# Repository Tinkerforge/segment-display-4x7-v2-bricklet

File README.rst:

Segment Display 4x7 Bricklet 2.0
================================

This repository contains the firmware source code and the hardware design
files. The documentation generator configs can be found at
https://github.com/Tinkerforge/generators

Repository Content
------------------

software/:
 * examples/: Examples for all supported languages
 * build/: Compiled files
 * src/: Source code of firmware
 * Makefile: Makefile to build project

hardware/:
 * Contains KiCad project files and additionally schematics as PDF

datasheets/:
 * Contains datasheets for sensors and complex ICs that are used

Hardware
--------

The hardware is designed with the open source EDA Suite KiCad
(http://www.kicad.org). Before you are able to open the files,
you have to install the Tinkerforge kicad-libraries
(https://github.com/Tinkerforge/kicad-libraries). You can either clone
them directly in hardware/ or clone them in a separate folder and
symlink them into hardware/
(ln -s kicad_path/kicad-libraries project_path/hardware). After that you
can open the .pro file in hardware/ with KiCad and from there view and
modify the schematics and the PCB layout.

Software
--------

If you want to do your own Brick/Bricklet firmware development we highly
recommend that you use our build environment setup script and read the
tutorial (https://www.tinkerforge.com/en/doc/Tutorials/Tutorial_Build_Environment/Tutorial.html).

To compile the C code we recommend you to install the newest GNU Arm Embedded
Toolchain (https://launchpad.net/gcc-arm-embedded/+download).
You also need to install bricklib2 (https://github.com/Tinkerforge/bricklib2).

You can either clone it directly in software/src/ or clone it in a
separate folder and symlink it into software/src/
(ln -s bricklib_path/bricklib2 project_path/software/src/). Finally make sure to
have CMake installed (http://www.cmake.org/cmake/resources/software.html).

After that you can build the firmware by invoking make in software/.
The firmware (.zbin) can then be found in software/build/ and uploaded
with brickv (click button "Flashing" on start screen).

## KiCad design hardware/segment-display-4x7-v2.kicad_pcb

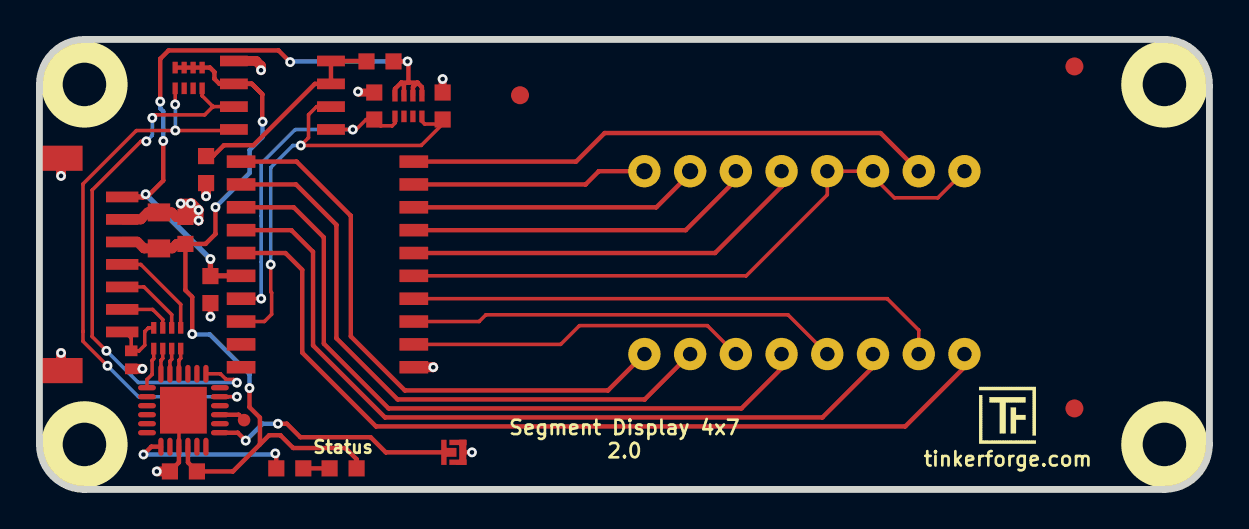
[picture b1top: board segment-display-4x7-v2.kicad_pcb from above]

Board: 2 copper layers, 65.0 x 25.0 mm, 30 parts (0 on the bottom side), 34 nets.

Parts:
C1, C3: 1nF; C0603F
C2: 220pF; C0402F
C4: 10uF; C0805
C5, C7, C8: 100nF; C0603F
C6: 1uF; C0603F
D1: blue; D0603F
Fiducial_Mark: VAL**; Fiducial_Mark
Fiducial_Mark#2, Fiducial_Mark#3: VAL**; Fiducial_Mark
P1: CON-SENSOR2
P2: DEBUG; DEBUG_PAD
P3: BOOT; SolderJumper
R1: 1k; R0603F
R2: 200k; R0603F
RP1: 82; 4X0402
RP2, RP3: 2k2; 4X0402
U1: XMC1100; QFN24-4x4mm-0.5mm
U2: TM1637; SOP20
U3: SEGMENT_4X7
U4, U5, U6, U7: DRILL; DRILL_NP
U8: PCA9306D; SOIC8
VAL: WEEE_7mm
VAL#2: CE_5mm

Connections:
+5V: C5.1, P1.1, R2.2, RP2.1, RP2.2, RP2.3, RP2.4, U2.16
COM1: U2.11, U3.1
COM2: U2.12, U3.2
COM3: U2.14, U3.6
COM4: U2.15, U3.8
COMD1D2: U2.13, U3.4
COMD3: U2.10, U3.10
GND: C1.1, C2.2, C3.1, C4.2, C5.2, C6.2, C7.2, C8.2, P1.2, P1.EP, P3.1, U1.9, U1.EXP, U2.1, U8.1
unnamed: C2.1, P1.7, RP1.4
unnamed: C8.1, R2.1, U8.7, U8.8
unnamed: D1.2, R1.2
unnamed: P1.4, RP1.1
unnamed: P1.5, RP1.2
unnamed: P1.6, RP1.3
unnamed: P2.1, U1.15
unnamed: P3.2, U1.13
unnamed: R1.1, U1.7
unnamed: U2.2, U3.3
unnamed: U2.3, U3.5
unnamed: U2.4, U3.7
unnamed: U2.5, U3.9, U3.11, U3.12
unnamed: U2.6, U3.13
unnamed: U2.7, U3.14
unnamed: U2.8, U3.15
unnamed: U2.9, U3.16
S-CLK: RP1.7, U1.23
S-CS: RP1.8, U1.22
S-MISO: RP1.5, U1.1
S-MOSI: RP1.6, U1.24
SCL: RP3.8, U1.19, U8.3
SCL2: C3.2, RP2.8, U2.18, U8.6
SDA: RP3.5, U1.17, U8.4
SDA2: C1.2, RP2.5, U2.17, U8.5
VCC: C4.1, C6.1, C7.1, D1.1, P1.3, RP3.1, RP3.2, RP3.3, RP3.4, U1.10, U8.2

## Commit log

2018-06-25 Add datasheets
2018-06-25 Use English language datasheet instead of Chinese
2018-06-25 Add schematic
2018-06-25 Rename files
2018-06-25 Add layout (tbc)
2018-06-27 Add layout
2018-06-28 Fix readme
2018-06-28 Add .gitignore
2018-07-04 Change value and size of pullup
2018-07-11 Add pullup resistors and change existing footprint to 4X0402
2018-07-11 Fix origin
2018-07-25 Add auto-generated stub firmware
2019-01-11 Add PCA9306 datasheet
2019-01-17 fix library links in schematic
2019-01-17 segment driver reconnect, control all available leds
2019-01-22 remove open gnd circuit
2019-02-21 Add API implementation and TM1637 driver
2019-02-21 Replace KHN40392ASR1D-2 with LTC-4627JR
2019-02-22 changed processor to XMC1100
2019-02-25 Fix segments for colon dots and tick mark
2019-02-25 Remove unnecessary comments
2019-03-28 mqtt: Fix whitespace.
2019-03-29 Add examples.
2019-04-23 Use bool for segment
2019-04-23 Add TM1637 config
2019-04-23 Turn off colon and tick when setting counter
2019-04-23 Fix function name
2019-04-23 Fix value/segment type mixup
2019-04-30 Turn logging off
2019-05-09 add schematic and sym lib
2019-05-10 add cutout drawing
2019-05-13 add 3d files, rename
2019-05-13 fix file names
2019-05-20 Update auto-generated rust example
2019-05-20 Release Bricklet
2019-05-20 Use correct hash for v2.0.0
2019-05-20 rust: Use merged imports again.
2019-05-20 shell: Escape positional argument to avoid option parsing
2019-05-29 Increase version for new release (changes in bricklib2)
2019-05-29 Add rev to changelog
2020-01-13 examples: Use python3 input instead of python2 raw_input.
2020-01-13 examples: mqtt: Remove trailing whitespace.
2020-03-16 Whitespace
2020-03-23 mqtt: Update for loop style
2020-04-07 examples: rust: Always block when calling bindings functions.
2020-08-19 Add uc examples.
2020-08-25 uc: Fix whitespace
2020-08-27 uc: Fix warnings.
2020-09-02 uc: Add example driver note.
2021-10-25 Update KiCad link
    https://www.kicad.org/blog/2021/10/Avoid-links-to-former-kicad-domain/
2022-04-19 examples: uc: Rename TF_HalContext to TF_HAL.
2022-04-27 uc: Adapt to bindings changes
2022-07-06 Add license files.
2025-10-04 Fix compatibility with new Docker build image (GCC 14.2.1)

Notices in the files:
hardware/segment-display-4x7-v2.kicad_pcb:
Licensed under CERN OHL v.1.1
Copyright (©) 2018, L.Lauer
Copyright Tinkerforge GmbH 2018.
This documentation describes Open Hardware and is licensed under the
CERN OHL v. 1.1.
